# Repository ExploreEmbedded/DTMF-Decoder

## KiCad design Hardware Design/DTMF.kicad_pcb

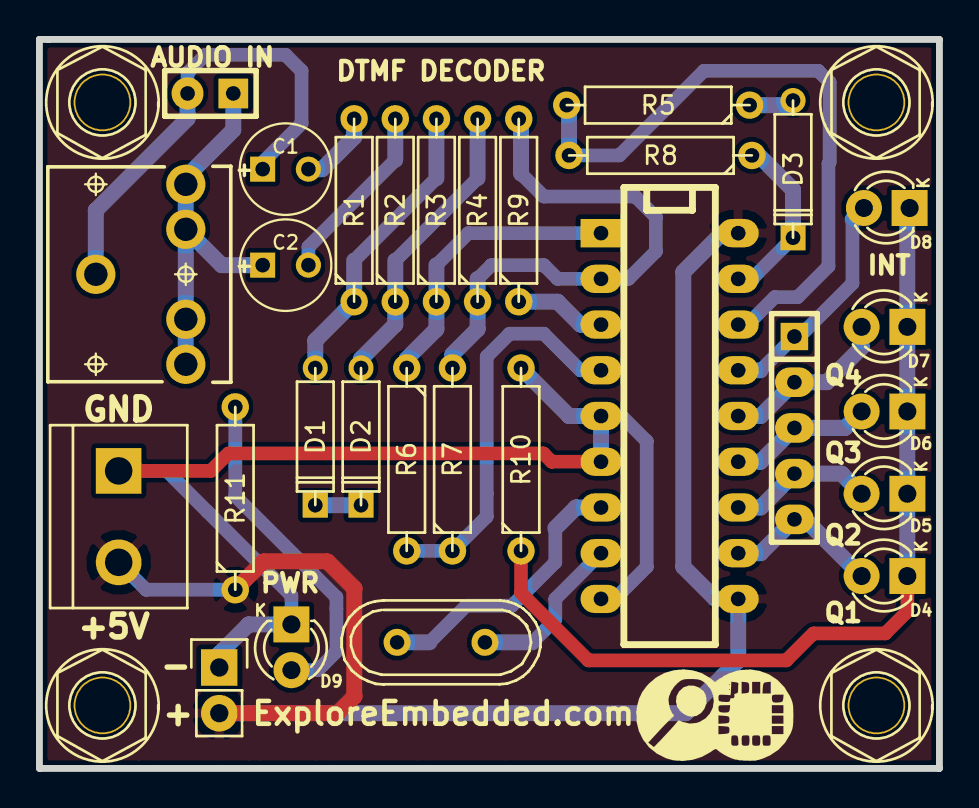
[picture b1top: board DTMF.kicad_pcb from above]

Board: 2 copper layers, 50.0 x 40.5 mm, 34 parts (0 on the bottom side), 25 nets.

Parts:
C1, C2: 10uF; C1V5
D1, D2: 5.6V; D3
D3: 1N14148; D3
D4: Q1; LED-3MM
D5: Q2; LED-3MM
D6: Q3; LED-3MM
D7: Q4; LED-3MM
D8: int; LED-3MM
D9: pwr; LED-3MM
IC1: MT8870P; DIP-18__300_ELL
P1: POWER 5V; bornier2
P2: AUDIO_IN; SIL-2
P3: OUTPUT; SIL-5
P4: CONN_01X02; Pin_Header_Straight_1x02
P5, P6, P7, P8: CONN_01X01; M3_mounting
R1, R2, R3, R4: 56K; R4
R5: 330K; R4
R6: 47K; R4
R7: 68K; R4
R8: 100K; R4
R9: 150k; R4
R10, R11: 470; R4
U1: 3.5MM_JACK; SparkFun-AUDIO-JACK
VAL: REF; Logo_8
X1: 3.5795MHz; Crystal_HC49-U_Vertical

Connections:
/INT: D8.1, IC1.15, P3.1
/Q1: D4.1, IC1.11, P3.5
/Q2: D5.1, IC1.12, P3.4
/Q3: D6.1, IC1.13, P3.3
/Q4: D7.1, IC1.14, P3.2
/vref: IC1.4, R6.2, R7.1
GND: D9.2, IC1.5, IC1.6, IC1.9, P1.1, P4.1, R10.2
unnamed: C1.1, P2.2, U1.1
unnamed: C1.2, R1.2
unnamed: C2.1, P2.1, U1.2, U1.3, U1.4, U1.5
unnamed: C2.2, R2.2
unnamed: D1.1, R1.1, R3.2
unnamed: D1.2, D2.2
unnamed: D2.1, R2.1, R4.2
unnamed: D3.1, R5.1
unnamed: D3.2, IC1.17, R8.1
unnamed: D4.2, D5.2, D6.2, D7.2, D8.2, R10.1
unnamed: D9.1, R11.2
unnamed: IC1.1, R3.1, R6.1
unnamed: IC1.2, R4.1, R7.2, R9.2
unnamed: IC1.3, R9.1
unnamed: IC1.7, X1.1
unnamed: IC1.8, X1.2
unnamed: IC1.16, R5.2, R8.2
VCC: IC1.10, IC1.18, P1.2, P4.2, R11.1

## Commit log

2016-09-14 Adeed design files
